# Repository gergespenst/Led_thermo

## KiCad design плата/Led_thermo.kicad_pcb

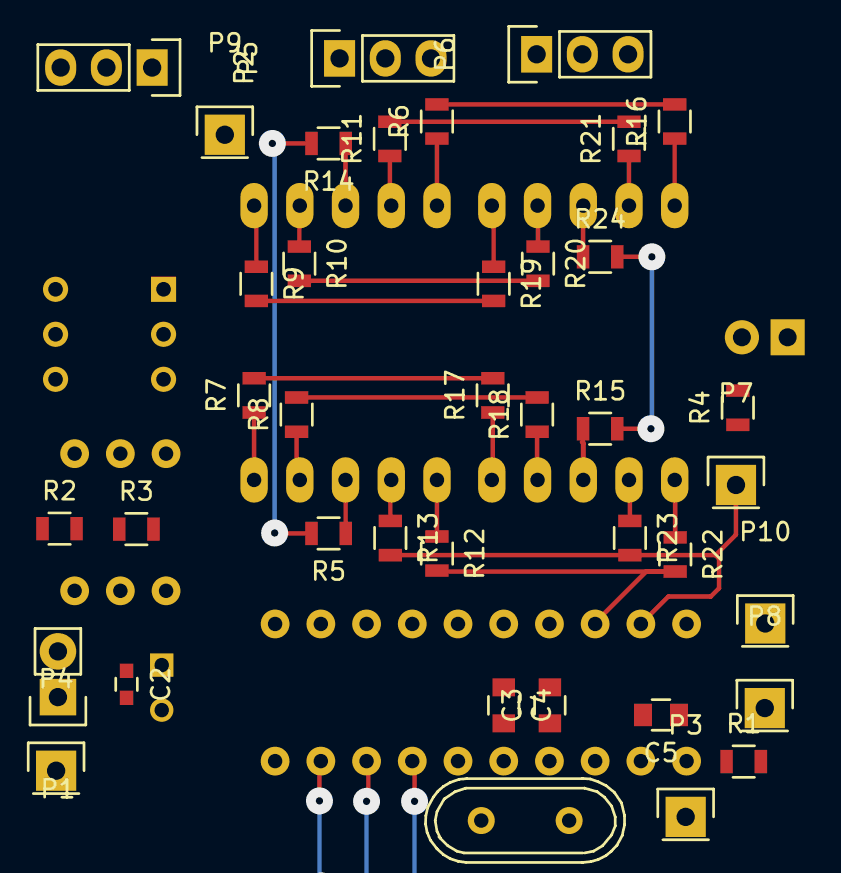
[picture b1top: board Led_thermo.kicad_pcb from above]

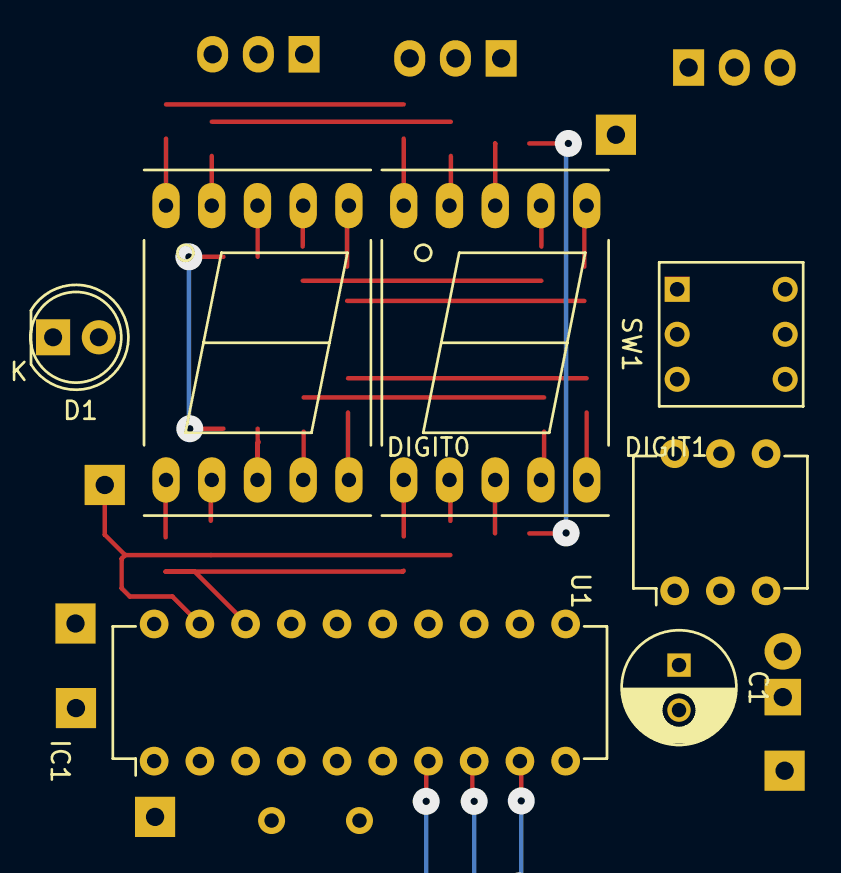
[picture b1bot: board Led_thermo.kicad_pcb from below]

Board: 2 copper layers, 46 parts (7 on the bottom side), 43 nets.

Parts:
C1: C; C_Radial_D6.3_L11.2_P2.5
C2: C; C_0603
C3, C4: C_Small; C_0805
C5: C; C_0805
D1: LED; LED-5MM
DIGIT0, DIGIT1: 7SEGM; 7SegmentLED_LTS6760_LTS6780
IC1: AT90S2313-P; DIP-20_W7.62mm
P1: CONN_01X02; Pin_Header_Straight_1x02
P2, P5, P6: CONN_01X03; Pin_Header_Straight_1x03
P3, P4, P7, P8, P9, P10: CONN_01X01; Pin_Header_Straight_1x01
R1, R2, R3, R4, R5, R6, R7, R8, R9, R10, R11, R12, R13, R14, R15, R16, R17, R18, R19, R20, R21, R22, R23, R24: R; R_0805
SW1: SW_PUSH; SW_PUSH_x2
U1: 4N25; DIP-6_W7.62mm
Y1: Crystal; Crystal_HC49-U_Vertical

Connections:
+5V: C1.1, C2.1, IC1.20, P1.2, P10.1, R1.2, U1.5
GND: C1.2, C2.2, C3.2, C4.1, C5.2, IC1.10, P1.1, P2.3, P4.1, P5.3, P6.3, R3.2, SW1.1
unnamed: C3.1, IC1.4, Y1.1
unnamed: C4.2, IC1.5, Y1.2
unnamed: C5.1, IC1.1, P3.1, R1.1
unnamed: D1.1, IC1.12, R6.2, R16.2
unnamed: D1.2, R4.2
unnamed: DIGIT0.1, R19.1
unnamed: DIGIT0.2, R20.1
unnamed: DIGIT0.3, R24.1
unnamed: DIGIT0.4, R21.1
unnamed: DIGIT0.5, R16.1
unnamed: DIGIT0.6, R22.1
unnamed: DIGIT0.7, R23.1
unnamed: DIGIT0.8, R15.1
unnamed: DIGIT0.9, R18.1
unnamed: DIGIT0.10, R17.1
unnamed: DIGIT1.1, R9.1
unnamed: DIGIT1.2, R10.1
unnamed: DIGIT1.3, R14.1
unnamed: DIGIT1.4, R11.1
unnamed: DIGIT1.5, R6.1
unnamed: DIGIT1.6, R12.1
unnamed: DIGIT1.7, R13.1
unnamed: DIGIT1.8, R5.1
unnamed: DIGIT1.9, R8.1
unnamed: DIGIT1.10, R7.1
unnamed: IC1.2, U1.1
unnamed: IC1.3, P2.1
unnamed: IC1.6, SW1.2
unnamed: IC1.7, P5.2, P6.2, R2.1
unnamed: IC1.8, R4.1
unnamed: IC1.9, R15.2, R24.2
unnamed: IC1.11, R5.2, R14.2
unnamed: IC1.13, R7.2, R17.2
unnamed: IC1.14, R8.2, R18.2
unnamed: IC1.15, R9.2, R19.2
unnamed: IC1.16, R10.2, R20.2
unnamed: IC1.17, P9.1, R11.2, R21.2
unnamed: IC1.18, P8.1, R12.2, R22.2
unnamed: IC1.19, P7.1, R13.2, R23.2
unnamed: P2.2, P5.1, P6.1, R2.2, U1.4
unnamed: R3.1, U1.2

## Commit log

2016-02-04 Работает чтение и поиск датчиков. Динамическое отображение цифр на индикаторе.
2016-02-04 Добавлены таймеры и сон. Пока не работает.
2016-02-05 В протеусе работает как надо. Спит и просыпается для отправки данных. Просыпается по нажатию кнопки.
2016-02-08 Исправлено количество отображаемых датчиков (раньше при одном показывались данные двух). Нарисована схема и печатная плата.
